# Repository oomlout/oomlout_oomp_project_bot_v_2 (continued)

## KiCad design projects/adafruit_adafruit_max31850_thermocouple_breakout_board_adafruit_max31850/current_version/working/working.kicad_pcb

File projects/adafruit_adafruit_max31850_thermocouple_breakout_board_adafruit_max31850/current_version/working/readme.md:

# adafruit_max31850_thermocouple_breakout_board
 
## summary 
* id: adafruit_adafruit_max31850_thermocouple_breakout_board_adafruit_max31850
* user: adafruit
* name: adafruit_max31850_thermocouple_breakout_board
* board: adafruit_max31850
* repo: https://github.com/adafruit/Adafruit-MAX31850-thermocouple-breakout-board

* src_file_repo_sch: 
* src_file_repo_sch_link: https://github.com/adafruit/Adafruit-MAX31850-thermocouple-breakout-board/tree/master/
* full details link: https://github.com/oomlout/oomlout_oomp_project_bot_v_2/tree/main/projects/adafruit_adafruit_max31850_thermocouple_breakout_board_adafruit_max31850/current_version/working  

## schematic  
  
[schematic (pdf)](working_schematic.pdf) 

## pcb  

[board (pdf)](working.pdf)  

## working_bom
| Id | Designator | Footprint | Quantity | Designation | Supplier and ref |  | None | 
| --- | --- | --- | --- | --- | --- | --- | --- | 
| 1 | FB2,FB1 | 0805 | 2 | Ferrite |  |  | [''] | 
| 2 | C1,C2 | 0805-NO | 2 | 10uF |  |  | [''] | 
| 3 | X1 | TERMBLOCK_1X2-3.5MM | 1 | 3.5mm |  |  | [''] | 
| 4 | U2 | SOT23-5 | 1 | MIC5225-3.3 |  |  | [''] | 
| 5 | JP1 | 1X08_ROUND_70 | 1 | Breakout |  |  | [''] | 
| 6 | FID2,FID1 | FIDUCIAL_1MM | 2 | FIDUCIAL" |  |  | [''] | 
| 7 | U$9,U$8 | MOUNTINGHOLE_2.5_PLATED | 2 | MOUNTINGHOLE2.5 |  |  | [''] | 
| 8 | U$19,U$18 | ADAFRUIT_3.5MM | 2 |  |  |  | [''] | 
| 9 | C3 | 0805-NO | 1 | 0.1uF |  |  | [''] | 
| 10 | U1 | TDFN10_3X4MM | 1 | MAX31850 |  |  | [''] | 
| 11 | SJ3,SJ4,SJ2,SJ1 | SOLDERJUMPER_2WAY_OPEN_NOPASTE | 4 |  |  |  | [''] | 

## bom_schematic
| Ref | Qnty | Value | Cmp name | Footprint | Description | Vendor | DNP | 
| --- | --- | --- | --- | --- | --- | --- | --- | 
| C1, C2 | 2 | 10uF | CAP_CERAMIC0805-NOOUTLINE | working:0805-NO |  |  |  | 
| C3 | 1 | 0.1uF | CAP_CERAMIC0805-NOOUTLINE | working:0805-NO |  |  |  | 
| FB1, FB2 | 2 | Ferrite | FERRITE0805 | working:0805 |  |  |  | 
| FID1, FID2 | 2 | FIDUCIAL"" | FIDUCIAL{dblquote}{dblquote} | working:FIDUCIAL_1MM |  |  |  | 
| JP1 | 1 | Breakout | HEADER-1X870MIL | working:1X08_ROUND_70 |  |  |  | 
| SJ1, SJ2, SJ3, SJ4 | 4 | SOLDERJUMPER_2WAY | SOLDERJUMPER_2WAY | working:SOLDERJUMPER_2WAY_OPEN_NOPASTE |  |  |  | 
| U1 | 1 | MAX31850 | MAX3185X | working:TDFN10_3X4MM |  |  |  | 
| U2 | 1 | MIC5225-3.3 | VREG_SOT23-5 | working:SOT23-5 |  |  |  | 
| U$8, U$9 | 2 | MOUNTINGHOLE2.5 | MOUNTINGHOLE2.5 | working:MOUNTINGHOLE_2.5_PLATED |  |  |  | 
| X1 | 1 | 3.5mm | TERMBLOCK_1X2 | working:TERMBLOCK_1X2-3.5MM |  |  |  | 

## mounting_holes
| x | y | package | value | ref | size | 
| --- | --- | --- | --- | --- | --- | 
| 15.24 | 0.0 | MOUNTINGHOLE_2.5_PLATED | MOUNTINGHOLE2.5 | U$8 | m3 | 
| 0.0 | 0.0 | MOUNTINGHOLE_2.5_PLATED | MOUNTINGHOLE2.5 | U$9 | m3 |

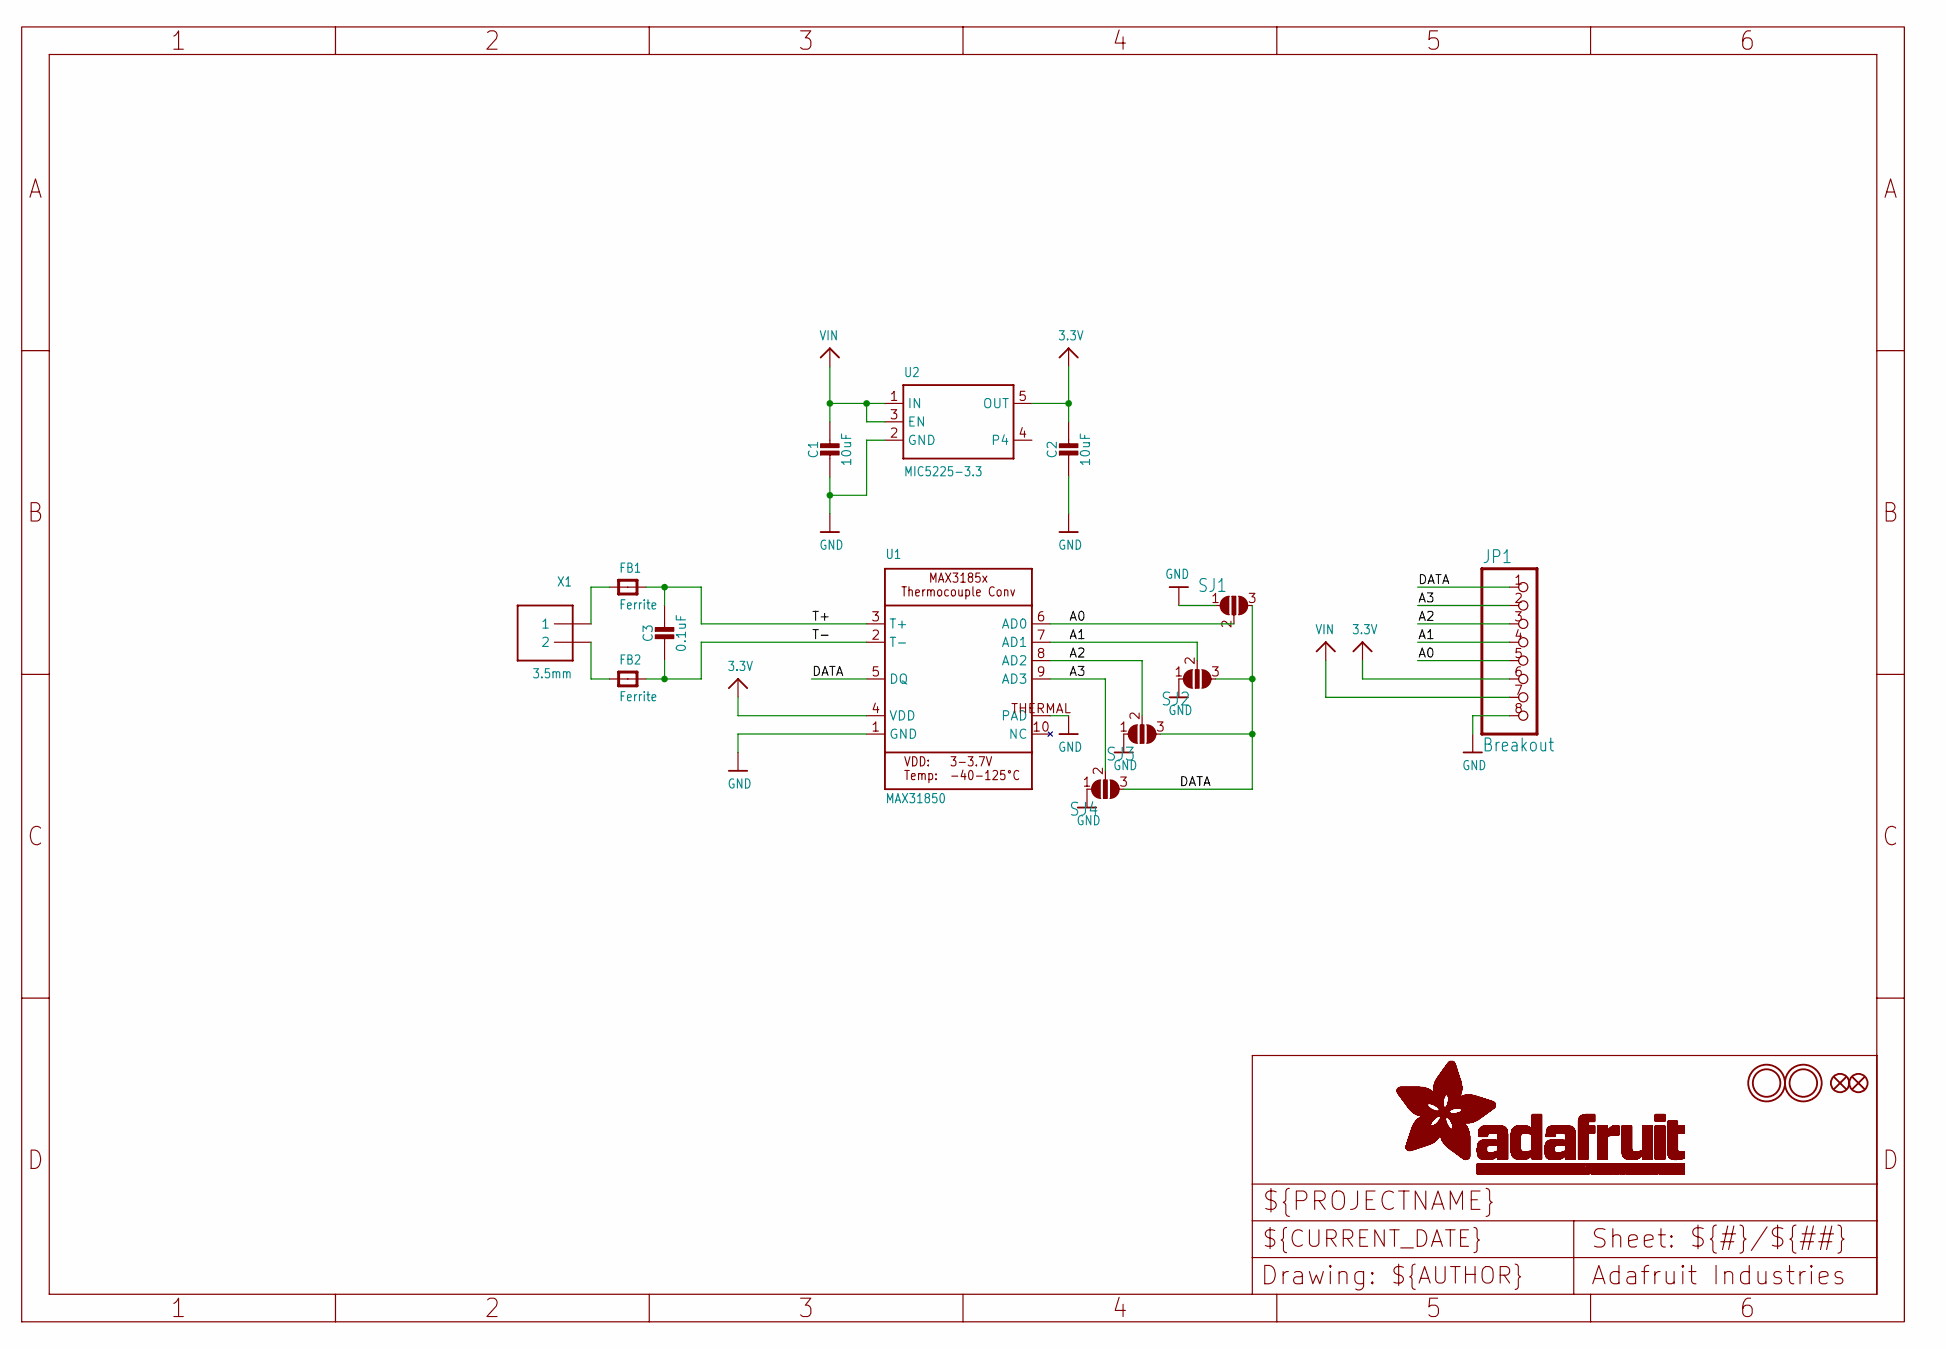
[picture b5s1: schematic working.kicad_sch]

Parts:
C1, C2: 10uF; 0805-NO
C3: 0.1uF; 0805-NO
FB1, FB2: Ferrite; 0805
FID1, FID2: FIDUCIAL""; FIDUCIAL_1MM
JP1: Breakout; 1X08_ROUND_70
SJ1, SJ2, SJ3, SJ4: SOLDERJUMPER_2WAY; SOLDERJUMPER_2WAY_OPEN_NOPASTE
U1: MAX31850; TDFN10_3X4MM
U2: MIC5225-3.3; SOT23-5
U$8, U$9: MOUNTINGHOLE2.5; MOUNTINGHOLE_2.5_PLATED
X1: 3.5mm; TERMBLOCK_1X2-3.5MM

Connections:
3.3V: C2.1, JP1.6, U1.4 (VDD), U2.5 (OUT)
A0: JP1.5, SJ1.2, U1.6 (AD0)
A1: JP1.4, SJ2.2, U1.7 (AD1)
A2: JP1.3, SJ3.2, U1.8 (AD2)
A3: JP1.2, SJ4.2, U1.9 (AD3)
DATA: JP1.1, SJ1.3, SJ2.3, SJ3.3, SJ4.3, U1.5 (DQ)
GND: C1.2, C2.2, JP1.8, SJ1.1, SJ2.1, SJ3.1, SJ4.1, U1.1 (GND), U1.THERMAL (PAD), U2.2 (GND)
unnamed: FB1.1, X1.1
unnamed: FB2.1, X1.2
T+: C3.1, FB1.2, U1.3 (T+)
T-: C3.2, FB2.2, U1.2 (T-)
VIN: C1.1, JP1.7, U2.1 (IN), U2.3 (EN)

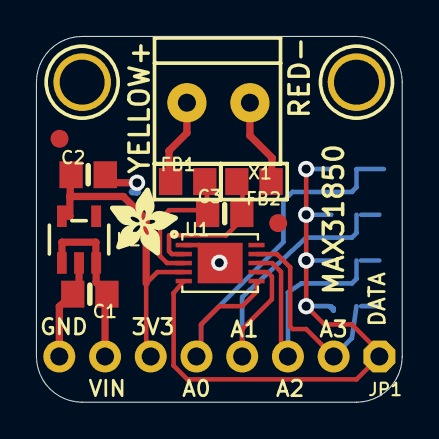
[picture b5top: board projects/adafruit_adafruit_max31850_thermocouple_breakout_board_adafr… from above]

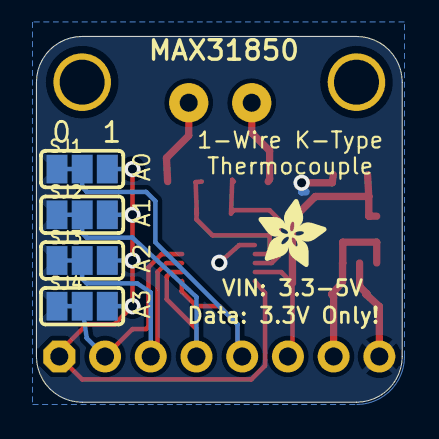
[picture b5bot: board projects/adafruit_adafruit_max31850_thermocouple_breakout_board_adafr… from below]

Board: 2 copper layers, 20.3 x 20.3 mm, 19 parts (5 on the bottom side), 12 nets.

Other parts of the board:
U$18, U$19: ADAFRUIT_3.5MM

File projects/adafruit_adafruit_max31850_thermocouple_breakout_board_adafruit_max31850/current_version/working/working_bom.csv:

"Id";"Designator";"Footprint";"Quantity";"Designation";"Supplier and ref";
1;"FB2,FB1";"0805";2;"Ferrite";;;
2;"C1,C2";"0805-NO";2;"10uF";;;
3;"X1";"TERMBLOCK_1X2-3.5MM";1;"3.5mm";;;
4;"U2";"SOT23-5";1;"MIC5225-3.3";;;
5;"JP1";"1X08_ROUND_70";1;"Breakout";;;
6;"FID2,FID1";"FIDUCIAL_1MM";2;"FIDUCIAL""";;;
7;"U$9,U$8";"MOUNTINGHOLE_2.5_PLATED";2;"MOUNTINGHOLE2.5";;;
8;"U$19,U$18";"ADAFRUIT_3.5MM";2;"";;;
9;"C3";"0805-NO";1;"0.1uF";;;
10;"U1";"TDFN10_3X4MM";1;"MAX31850";;;
11;"SJ3,SJ4,SJ2,SJ1";"SOLDERJUMPER_2WAY_OPEN_NOPASTE";4;"";;;

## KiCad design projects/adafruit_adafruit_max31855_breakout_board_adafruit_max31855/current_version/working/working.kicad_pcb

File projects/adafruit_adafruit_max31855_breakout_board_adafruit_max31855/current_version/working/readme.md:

# adafruit_max31855_breakout_board
 
## summary 
* id: adafruit_adafruit_max31855_breakout_board_adafruit_max31855
* user: adafruit
* name: adafruit_max31855_breakout_board
* board: adafruit_max31855
* repo: https://github.com/adafruit/Adafruit-MAX31855-breakout-board

* src_file_repo_sch: 
* src_file_repo_sch_link: https://github.com/adafruit/Adafruit-MAX31855-breakout-board/tree/master/
* full details link: https://github.com/oomlout/oomlout_oomp_project_bot_v_2/tree/main/projects/adafruit_adafruit_max31855_breakout_board_adafruit_max31855/current_version/working  

## schematic  
  
[schematic (pdf)](working_schematic.pdf) 

## pcb  

[board (pdf)](working.pdf)  

## working_bom
| Id | Designator | Footprint | Quantity | Designation | Supplier and ref |  | None | 
| --- | --- | --- | --- | --- | --- | --- | --- | 
| 1 | D1 | SOD-323F | 1 | 1n4148 |  |  | [''] | 
| 2 | U$5,U$4 | MOUNTINGHOLE_2.0_PLATED | 2 | MOUNTINGHOLE2.0 |  |  | [''] | 
| 3 | C3 | _0805 | 1 | 0.01ÂµF |  |  | [''] | 
| 4 | R2,R1 | R0805 | 2 | 10K |  |  | [''] | 
| 5 | U$1,U$2 | FIDUCIAL_1MM | 2 | FIDUCIAL |  |  | [''] | 
| 6 | JP1 | 1X06_ROUND_76 | 1 | Breakout |  |  | [''] | 
| 7 | J1 | 1X2-3.5MM | 1 | 1X2-3.5MM |  |  | [''] | 
| 8 | D2 | SOD-323F | 1 | 1N4148 |  |  | [''] | 
| 9 | FB2,FB1 | _0805 | 2 | Ferrite |  |  | [''] | 
| 10 | C2,C1 | C0805K | 2 | 10uF |  |  | [''] | 
| 11 | IC1 | SO08 | 1 | MAX31855 |  |  | [''] | 
| 12 | IC2 | SOT23-5L | 1 | LP298XS |  |  | [''] | 
| 13 | U$6 | ADAFRUIT_3.5MM | 1 |  |  |  | [''] | 

## bom_schematic
| Ref | Qnty | Value | Cmp name | Footprint | Description | Vendor | DNP | 
| --- | --- | --- | --- | --- | --- | --- | --- | 
| C1, C2 | 2 | 10uF | C-USC0805K | working:C0805K |  |  |  | 
| C3 | 1 | 0.01ÂµF | CAP_CERAMIC_0805 | working:_0805 |  |  |  | 
| D1 | 1 | 1n4148 | DIODESOD-323F | working:SOD-323F |  |  |  | 
| D2 | 1 | 1N4148 | DIODESOD-323F | working:SOD-323F |  |  |  | 
| FB1, FB2 | 2 | Ferrite | FERRITE_0805 | working:_0805 |  |  |  | 
| IC1 | 1 | MAX6675 | MAX6675 | working:SO08 |  |  |  | 
| IC2 | 1 | LP298XS | LP298XS | working:SOT23-5L |  |  |  | 
| J1 | 1 | 1X2-3.5MM | 1X2-3.5MM | working:1X2-3.5MM |  |  |  | 
| JP1 | 1 | Breakout | HEADER-1X676MIL | working:1X06_ROUND_76 |  |  |  | 
| R1, R2 | 2 | 10K | R-US_R0805 | working:R0805 |  |  |  | 
| U$1, U$2 | 2 | FIDUCIAL | FIDUCIAL | working:FIDUCIAL_1MM |  |  |  | 
| U$4, U$5 | 2 | MOUNTINGHOLE2.0 | MOUNTINGHOLE2.0 | working:MOUNTINGHOLE_2.0_PLATED |  |  |  | 

## mounting_holes
| x | y | package | value | ref | size | 
| --- | --- | --- | --- | --- | --- | 
| 15.24 | 0.0 | MOUNTINGHOLE_2.0_PLATED | MOUNTINGHOLE2.0 | U$4 | m3 | 
| 0.0 | 0.0 | MOUNTINGHOLE_2.0_PLATED | MOUNTINGHOLE2.0 | U$5 | m3 |

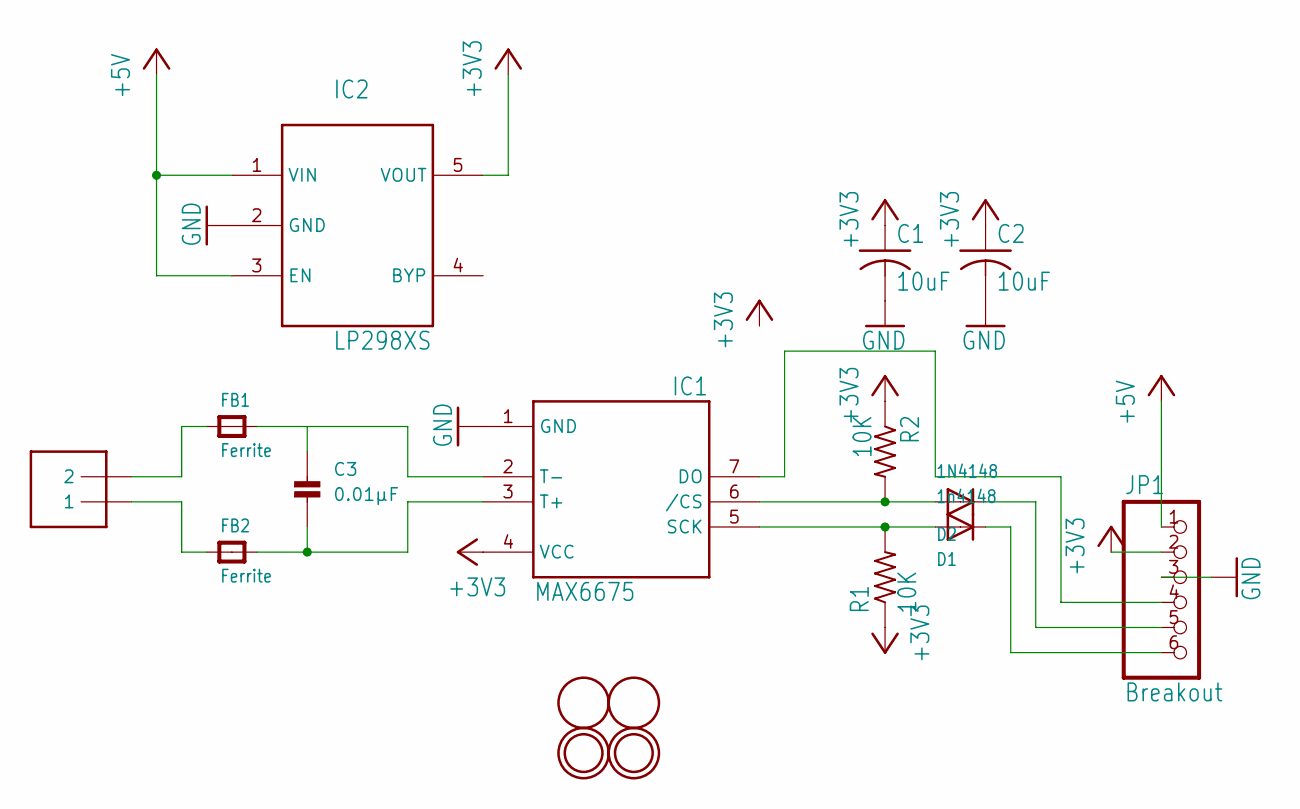
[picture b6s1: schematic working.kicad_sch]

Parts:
C1, C2: 10uF; C0805K
C3: 0.01µF; _0805
D1: 1n4148; SOD-323F
D2: 1N4148; SOD-323F
FB1, FB2: Ferrite; _0805
IC1: MAX6675; SO08
IC2: LP298XS; SOT23-5L
J1: 1X2-3.5MM
JP1: Breakout; 1X06_ROUND_76
R1, R2: 10K; R0805
U$1, U$2: FIDUCIAL; FIDUCIAL_1MM
U$4, U$5: MOUNTINGHOLE2.0; MOUNTINGHOLE_2.0_PLATED

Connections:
+3V3: C1.1, C2.1, IC1.4 (VCC), IC2.5 (VOUT), JP1.2, R1.1, R2.1
+5V: IC2.1 (VIN), IC2.3 (EN), JP1.1
CS: D2.A, IC1.6 (/CS), R2.2
DO: IC1.7 (DO), JP1.4
GND: C1.2, C2.2, IC1.1 (GND), IC2.2 (GND), JP1.3
unnamed: FB1.1, J1.2
unnamed: D2.C, JP1.5
unnamed: D1.C, JP1.6
unnamed: C3.1, FB1.2, IC1.2 (T-)
unnamed: FB2.1, J1.1
unnamed: C3.2, FB2.2, IC1.3 (T+)
SCK: D1.A, IC1.5 (SCK), R1.2

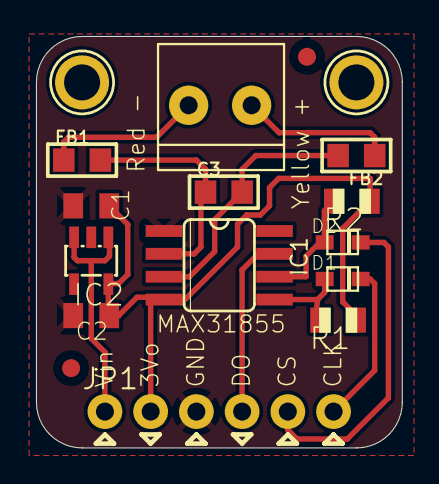
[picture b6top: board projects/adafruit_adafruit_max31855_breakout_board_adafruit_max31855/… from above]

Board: 16 copper layers, 20.3 x 22.9 mm, 18 parts (1 on the bottom side), 12 nets.

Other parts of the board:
U$6: ADAFRUIT_3.5MM

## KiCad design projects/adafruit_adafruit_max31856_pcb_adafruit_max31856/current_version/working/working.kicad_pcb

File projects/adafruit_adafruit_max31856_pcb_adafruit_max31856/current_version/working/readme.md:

# adafruit_max31856_pcb
 
## summary 
* id: adafruit_adafruit_max31856_pcb_adafruit_max31856
* user: adafruit
* name: adafruit_max31856_pcb
* board: adafruit_max31856
* repo: https://github.com/adafruit/Adafruit-MAX31856-PCB

* src_file_repo_sch: 
* src_file_repo_sch_link: https://github.com/adafruit/Adafruit-MAX31856-PCB/tree/master/
* full details link: https://github.com/oomlout/oomlout_oomp_project_bot_v_2/tree/main/projects/adafruit_adafruit_max31856_pcb_adafruit_max31856/current_version/working  

## schematic  
  
[schematic (pdf)](working_schematic.pdf) 

## pcb  

[board (pdf)](working.pdf)  

## working_bom
| Id | Designator | Footprint | Quantity | Designation | Supplier and ref |  | None | 
| --- | --- | --- | --- | --- | --- | --- | --- | 
| 1 | D2,D1,D3 | SOD-323 | 3 | 1N4148 |  |  | [''] | 
| 2 | R2,R1 | 0805-NO | 2 | 100 |  |  | [''] | 
| 3 | C1 | 0805_10MGAP | 1 | 0.01uF |  |  | [''] | 
| 4 | U$13,U$14 | MOUNTINGHOLE_2.5_PLATED | 2 | MOUNTINGHOLE2.5 |  |  | [''] | 
| 5 | C3 | 0805-NO | 1 | 0.01uF |  |  | [''] | 
| 6 | U2 | TSSOP14 | 1 | MAX31856 |  |  | [''] | 
| 7 | R5,R3,R4 | 0805-NO | 3 | 10K |  |  | [''] | 
| 8 | JP1 | 1X09_ROUND_70 | 1 |  |  |  | [''] | 
| 9 | X1 | TERMBLOCK_1X2-3.5MM | 1 | 3.5mm term |  |  | [''] | 
| 10 | U$23 | SYMBOL_PLUS | 1 |  |  |  | [''] | 
| 11 | FID2,FID1 | FIDUCIAL_1MM | 2 | FIDUCIAL" |  |  | [''] | 
| 12 | U$1 | PCBFEAT-REV-040 | 1 |  |  |  | [''] | 
| 13 | C7,C6 | 0805-NO | 2 | 10uF |  |  | [''] | 
| 14 | C2,C4,C5 | 0805-NO | 3 | 0.1uF |  |  | [''] | 
| 15 | U$24 | SYMBOL_MINUS | 1 |  |  |  | [''] | 
| 16 | U$25 | ADAFRUIT_3.5MM | 1 |  |  |  | [''] | 
| 17 | U1 | SOT23-5 | 1 | mic5225-3.3 |  |  | [''] | 
| 18 | U$26 | ADAFRUIT_TEXT_20MM | 1 |  |  |  | [''] | 

## bom_schematic
| Ref | Qnty | Value | Cmp name | Footprint | Description | Vendor | DNP | 
| --- | --- | --- | --- | --- | --- | --- | --- | 
| C1 | 1 | 0.01uF | CAP_CERAMIC0805_10MGAP | working:0805_10MGAP |  |  |  | 
| C2, C4, C5 | 3 | 0.1uF | CAP_CERAMIC0805-NOOUTLINE | working:0805-NO |  |  |  | 
| C3 | 1 | 0.01uF | CAP_CERAMIC0805-NOOUTLINE | working:0805-NO |  |  |  | 
| C6, C7 | 2 | 10uF | CAP_CERAMIC0805-NOOUTLINE | working:0805-NO |  |  |  | 
| D1, D2, D3 | 3 | 1N4148 | DIODESOD-323 | working:SOD-323 |  |  |  | 
| FID1, FID2 | 2 | FIDUCIAL"" | FIDUCIAL{dblquote}{dblquote} | working:FIDUCIAL_1MM |  |  |  | 
| JP1 | 1 | HEADER-1X970MIL | HEADER-1X970MIL | working:1X09_ROUND_70 |  |  |  | 
| R1, R2 | 2 | 100 | RESISTOR0805_NOOUTLINE | working:0805-NO |  |  |  | 
| R3, R4, R5 | 3 | 10K | RESISTOR0805_NOOUTLINE | working:0805-NO |  |  |  | 
| U1 | 1 | mic5225-3.3 | VREG_SOT23-5 | working:SOT23-5 |  |  |  | 
| U2 | 1 | MAX31856 | MAX31856 | working:TSSOP14 |  |  |  | 
| U$13, U$14 | 2 | MOUNTINGHOLE2.5 | MOUNTINGHOLE2.5 | working:MOUNTINGHOLE_2.5_PLATED |  |  |  | 
| X1 | 1 | 3.5mm term | TERMBLOCK_1X2 | working:TERMBLOCK_1X2-3.5MM |  |  |  | 

## mounting_holes
| x | y | package | value | ref | size | 
| --- | --- | --- | --- | --- | --- | 
| 0.0 | 0.0 | MOUNTINGHOLE_2.5_PLATED | MOUNTINGHOLE2.5 | U$13 | m3 | 
| 19.05 | 0.0 | MOUNTINGHOLE_2.5_PLATED | MOUNTINGHOLE2.5 | U$14 | m3 |

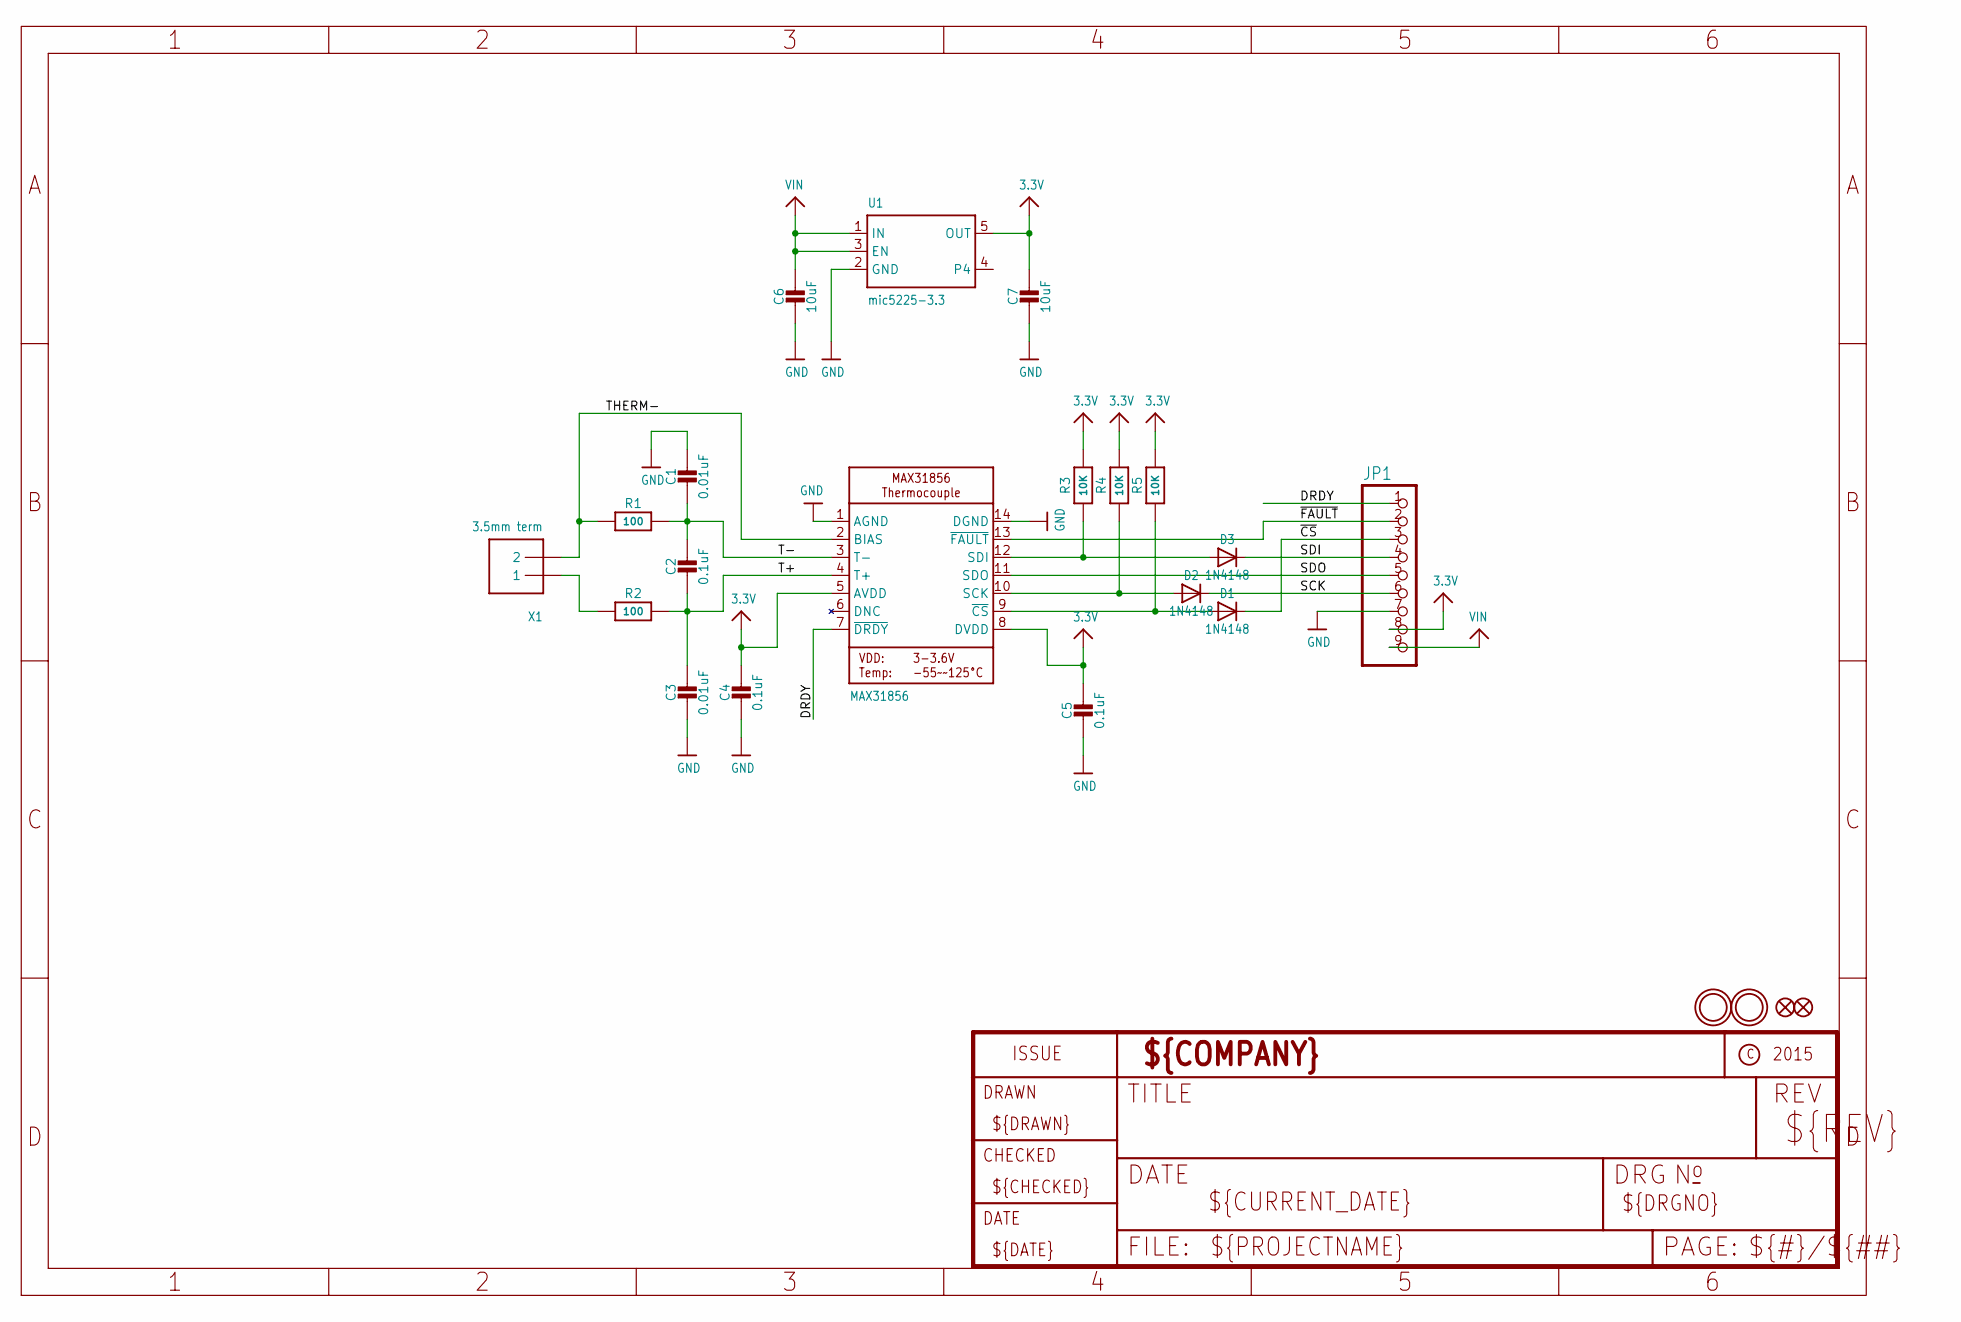
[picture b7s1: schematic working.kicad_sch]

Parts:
C1: 0.01uF; 0805_10MGAP
C2, C4, C5: 0.1uF; 0805-NO
C3: 0.01uF; 0805-NO
C6, C7: 10uF; 0805-NO
D1, D2, D3: 1N4148; SOD-323
FID1, FID2: FIDUCIAL""; FIDUCIAL_1MM
JP1: HEADER-1X970MIL; 1X09_ROUND_70
R1, R2: 100; 0805-NO
R3, R4, R5: 10K; 0805-NO
U1: mic5225-3.3; SOT23-5
U2: MAX31856; TSSOP14
U$13, U$14: MOUNTINGHOLE2.5; MOUNTINGHOLE_2.5_PLATED
X1: 3.5mm term; TERMBLOCK_1X2-3.5MM

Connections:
3.3V: C4.1, C5.1, C7.1, JP1.8, R3.2, R4.2, R5.2, U1.5 (OUT), U2.5 (AVDD), U2.8 (DVDD)
DRDY: JP1.1, U2.7 (~DRDY)
GND: C1.1, C3.2, C4.2, C5.2, C6.2, C7.2, JP1.7, U1.2 (GND), U2.1 (AGND), U2.14 (DGND)
SCK: D2.C, JP1.6
SCK_3V: D2.A, R4.1, U2.10 (SCK)
SDI: D3.C, JP1.4
SDO: JP1.5, U2.11 (SDO)
SDO_3V: D3.A, R3.1, U2.12 (SDI)
T+: C2.2, C3.1, R2.2, U2.4 (T+)
T-: C1.2, C2.1, R1.2, U2.3 (T-)
THERM+: R2.1, X1.1
THERM-: R1.1, U2.2 (BIAS), X1.2
VIN: C6.1, JP1.9, U1.1 (IN), U1.3 (EN)
~CS_3V: D1.A, R5.1, U2.9 (~CS)
~CS: D1.C, JP1.3
~FAULT: JP1.2, U2.13 (~FAULT)

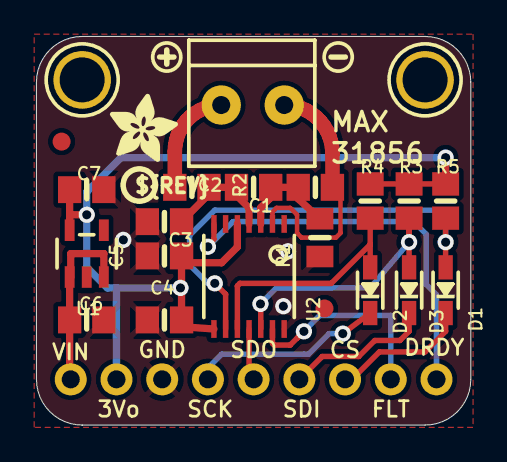
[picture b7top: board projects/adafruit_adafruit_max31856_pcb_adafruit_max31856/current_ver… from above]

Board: 2 copper layers, 24.1 x 21.6 mm, 28 parts (1 on the bottom side), 16 nets.

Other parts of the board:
U$1: PCBFEAT-REV-040
U$23: SYMBOL_PLUS
U$24: SYMBOL_MINUS
U$25: ADAFRUIT_3.5MM
U$26: ADAFRUIT_TEXT_20MM
